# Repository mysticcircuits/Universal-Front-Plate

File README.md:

# Universal-Front-Plate

The Universal front plate was a project that I had high hopes for and while it did not accomplish what I originally set out to do with it I still found it quite useful.  Basically the board has 16 of the same footprint which can fit either an erthenvar style 3.5" jack, a board mount alpha pot or a sideways SPDT toggle switch.  There is also a set of 8 LEDs and their dedicated current limiting resistors going down the middle and hooked up to a trimmer which controls the overall brightness. All of these components are wired to some headers going along each side of the board so that a component board can be attached.  My idea was that this project would allow people to breadboard their own ideas while having a simple board which could handle various panel configurations and also maybe have some panels with drill positions marked to make prototyping without panel wiring much quicker.  The problem became that components were crammed too close together: when pots are placed in adjacent positions, whether vertically or horizonally, knob tightness became a serious issue.  I could not use the space saving "plastic shaft" pots because the pots are oriented sideways and so the direction marker would be rotated by 90 degrees.  Even placing the pots diagonally posed some issues with spacing.  However I did make two designs with the UFP and I have a few more coming up, as well as possibly other version of the UFP which are less universal but which are more efficient in their use of space.

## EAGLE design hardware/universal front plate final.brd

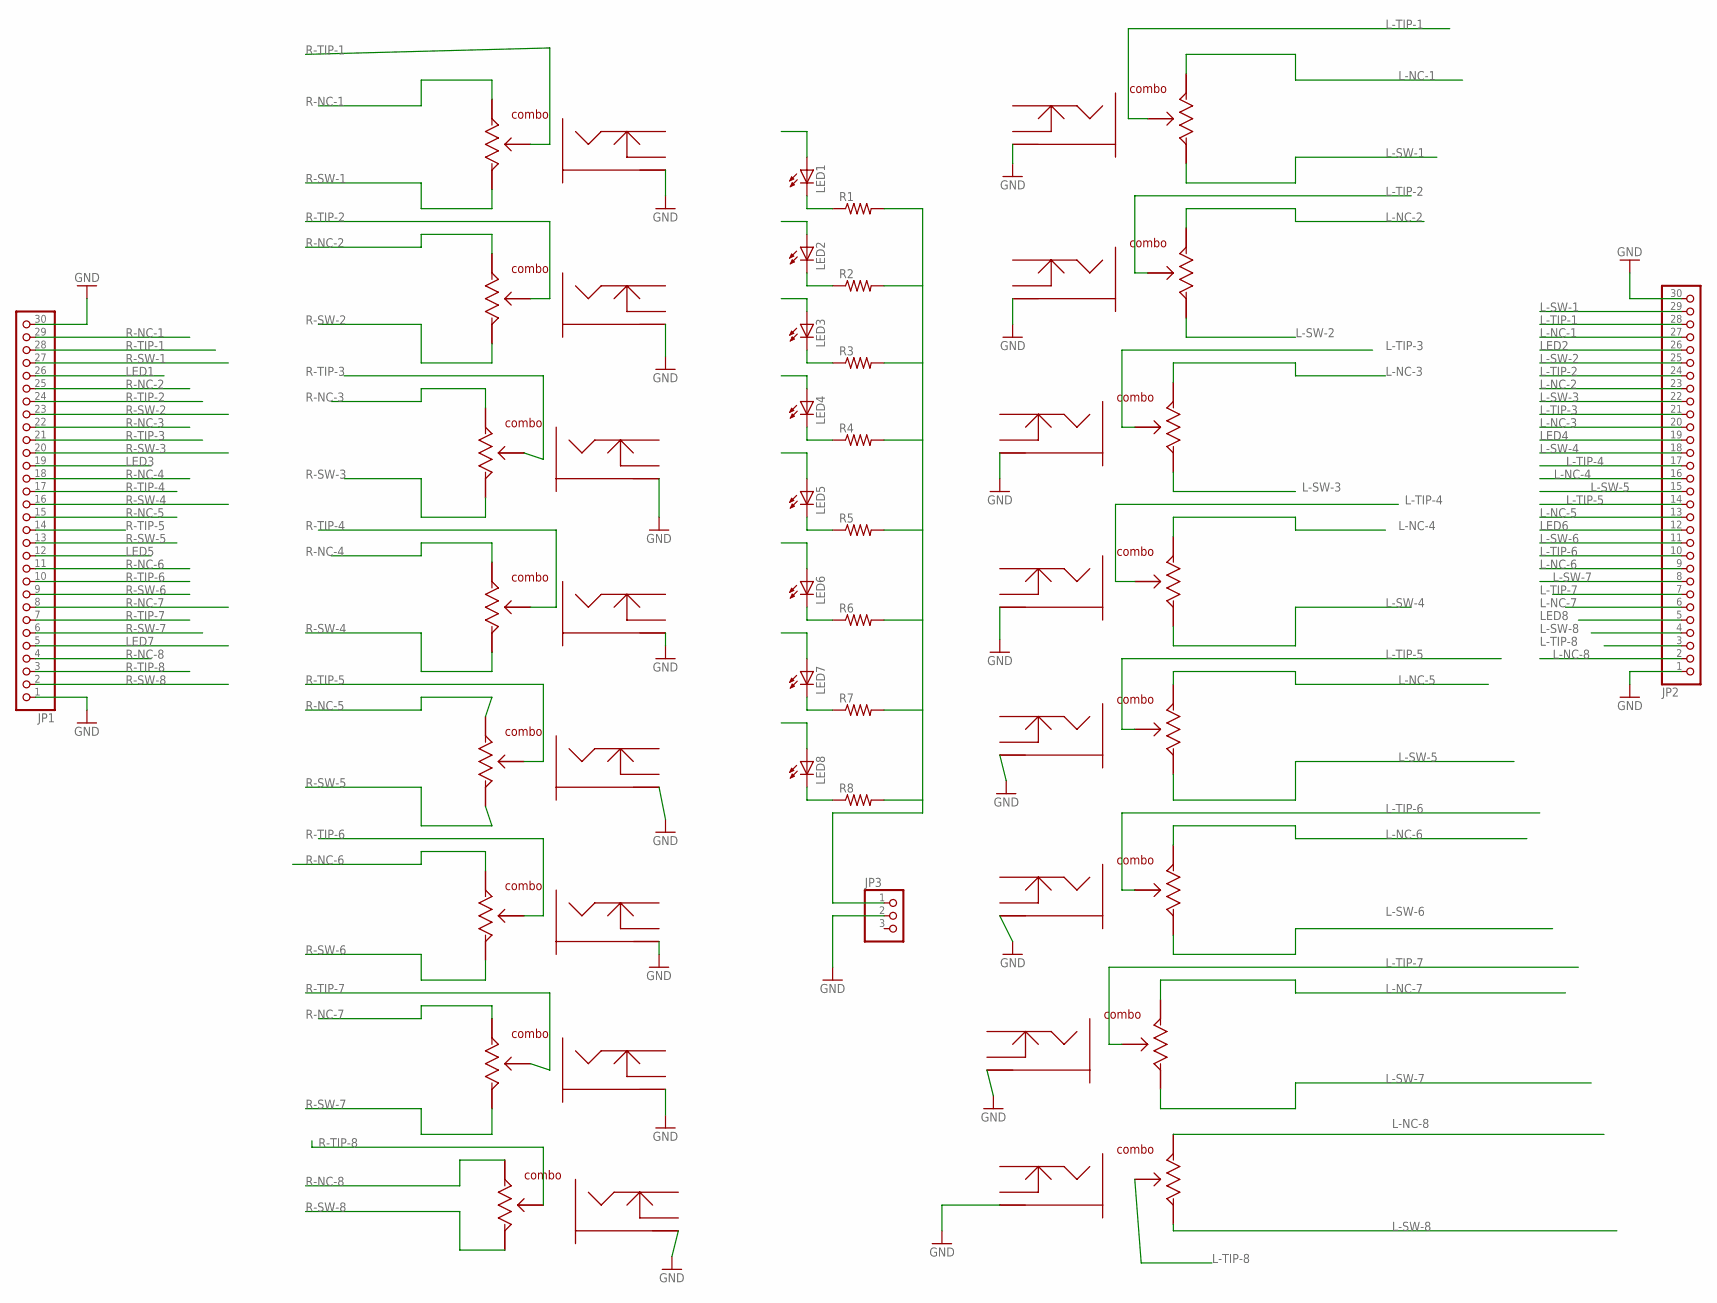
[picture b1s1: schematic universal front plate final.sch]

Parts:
JP1, JP2: PINHD-1X30; 1X30
JP3: PINHD-1X3; 1X03
LED1, LED2, LED3, LED4, LED5, LED6, LED7, LED8: LED3MM
R1, R2, R3, R4, R5, R6, R7, R8: R-US_0204/5; 0204/5
U$1, U$2, U$3, U$4, U$5, U$6, U$7, U$8, U$9, U$10, U$11, U$12, U$13, U$14, U$15, U$16: KOBICON-COMBO-NEW

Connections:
GND: JP1.1, JP1.30, JP2.1, JP2.30, JP3.2, U$1.GND (JACK-GND), U$1.GND2 (JACK-GND), U$2.GND (JACK-GND), U$2.GND2 (JACK-GND), U$3.GND (JACK-GND), U$3.GND2 (JACK-GND), U$4.GND (JACK-GND), U$4.GND2 (JACK-GND), U$5.GND (JACK-GND), U$5.GND2 (JACK-GND), U$6.GND (JACK-GND), U$6.GND2 (JACK-GND), U$7.GND (JACK-GND), U$7.GND2 (JACK-GND), U$8.GND (JACK-GND), U$8.GND2 (JACK-GND), U$9.GND (JACK-GND), U$9.GND2 (JACK-GND), U$10.GND (JACK-GND), U$10.GND2 (JACK-GND), U$11.GND (JACK-GND), U$11.GND2 (JACK-GND), U$12.GND (JACK-GND), U$12.GND2 (JACK-GND), U$13.GND (JACK-GND), U$13.GND2 (JACK-GND), U$14.GND (JACK-GND), U$14.GND2 (JACK-GND), U$15.GND (JACK-GND), U$15.GND2 (JACK-GND), U$16.GND (JACK-GND), U$16.GND2 (JACK-GND)
L-NC-1: JP2.27, U$8.JACK-MID (POT-L), U$8.POT-L
L-NC-2: JP2.23, U$9.JACK-MID (POT-L), U$9.POT-L
L-NC-3: JP2.20, U$10.JACK-MID (POT-L), U$10.POT-L
L-NC-4: JP2.16, U$11.JACK-MID (POT-L), U$11.POT-L
L-NC-5: JP2.13, U$12.JACK-MID (POT-L), U$12.POT-L
L-NC-6: JP2.9, U$13.JACK-MID (POT-L), U$13.POT-L
L-NC-7: JP2.6, U$14.JACK-MID (POT-L), U$14.POT-L
L-NC-8: JP2.2, U$15.JACK-MID (POT-L), U$15.POT-L
L-SW-1: JP2.29, U$8.JACK-BOT (POT-R), U$8.POT-R
L-SW-2: JP2.25, U$9.JACK-BOT (POT-R), U$9.POT-R
L-SW-3: JP2.22, U$10.JACK-BOT (POT-R), U$10.POT-R
L-SW-4: JP2.18, U$11.JACK-BOT (POT-R), U$11.POT-R
L-SW-5: JP2.15, U$12.JACK-BOT (POT-R), U$12.POT-R
L-SW-6: JP2.11, U$13.JACK-BOT (POT-R), U$13.POT-R
L-SW-7: JP2.8, U$14.JACK-BOT (POT-R), U$14.POT-R
L-SW-8: JP2.4, U$15.JACK-BOT (POT-R), U$15.POT-R
L-TIP-1: JP2.28, U$8.JACK-TOP (POT-MID), U$8.POT-MID
L-TIP-2: JP2.24, U$9.JACK-TOP (POT-MID), U$9.POT-MID
L-TIP-3: JP2.21, U$10.JACK-TOP (POT-MID), U$10.POT-MID
L-TIP-4: JP2.17, U$11.JACK-TOP (POT-MID), U$11.POT-MID
L-TIP-5: JP2.14, U$12.JACK-TOP (POT-MID), U$12.POT-MID
L-TIP-6: JP2.10, U$13.JACK-TOP (POT-MID), U$13.POT-MID
L-TIP-7: JP2.7, U$14.JACK-TOP (POT-MID), U$14.POT-MID
L-TIP-8: JP2.3, U$15.JACK-TOP (POT-MID), U$15.POT-MID
LED1: JP1.26, LED1.A
LED2: JP2.26, LED2.A
LED3: JP1.19, LED3.A
LED4: JP2.19, LED4.A
LED5: JP1.12, LED5.A
LED6: JP2.12, LED6.A
LED7: JP1.5, LED7.A
LED8: JP2.5, LED8.A
unnamed: LED8.K (C), R8.1
unnamed: JP3.1, R1.2, R2.2, R3.2, R4.2, R5.2, R6.2, R7.2, R8.2
unnamed: LED1.K (C), R1.1
unnamed: LED2.K (C), R2.1
unnamed: LED3.K (C), R3.1
unnamed: LED4.K (C), R4.1
unnamed: LED5.K (C), R5.1
unnamed: LED6.K (C), R6.1
unnamed: LED7.K (C), R7.1
R-NC-1: JP1.29, U$1.JACK-MID (POT-L), U$1.POT-L
R-NC-2: JP1.25, U$2.JACK-MID (POT-L), U$2.POT-L
R-NC-3: JP1.22, U$3.JACK-MID (POT-L), U$3.POT-L
R-NC-4: JP1.18, U$4.JACK-MID (POT-L), U$4.POT-L
R-NC-5: JP1.15, U$5.JACK-MID (POT-L), U$5.POT-L
R-NC-6: JP1.11, U$6.JACK-MID (POT-L), U$6.POT-L
R-NC-7: JP1.8, U$7.JACK-MID (POT-L), U$7.POT-L
R-NC-8: JP1.4, U$16.JACK-MID (POT-L), U$16.POT-L
R-SW-1: JP1.27, U$1.JACK-BOT (POT-R), U$1.POT-R
R-SW-2: JP1.23, U$2.JACK-BOT (POT-R), U$2.POT-R
R-SW-3: JP1.20, U$3.JACK-BOT (POT-R), U$3.POT-R
R-SW-4: JP1.16, U$4.JACK-BOT (POT-R), U$4.POT-R
R-SW-5: JP1.13, U$5.JACK-BOT (POT-R), U$5.POT-R
R-SW-6: JP1.9, U$6.JACK-BOT (POT-R), U$6.POT-R
R-SW-7: JP1.6, U$7.JACK-BOT (POT-R), U$7.POT-R
R-SW-8: JP1.2, U$16.JACK-BOT (POT-R), U$16.POT-R
R-TIP-1: JP1.28, U$1.JACK-TOP (POT-MID), U$1.POT-MID
R-TIP-2: JP1.24, U$2.JACK-TOP (POT-MID), U$2.POT-MID
R-TIP-3: JP1.21, U$3.JACK-TOP (POT-MID), U$3.POT-MID
R-TIP-4: JP1.17, U$4.JACK-TOP (POT-MID), U$4.POT-MID
R-TIP-5: JP1.14, U$5.JACK-TOP (POT-MID), U$5.POT-MID
R-TIP-6: JP1.10, U$6.JACK-TOP (POT-MID), U$6.POT-MID
R-TIP-7: JP1.7, U$7.JACK-TOP (POT-MID), U$7.POT-MID
R-TIP-8: JP1.3, U$16.JACK-TOP (POT-MID), U$16.POT-MID

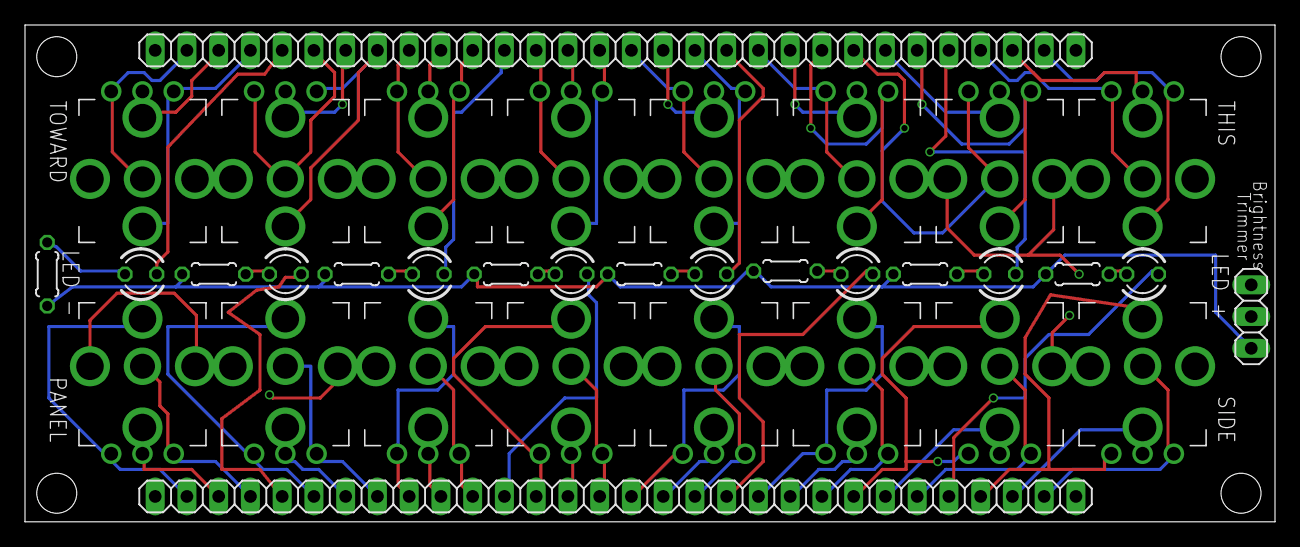
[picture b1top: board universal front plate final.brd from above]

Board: 2 copper layers, 100.0 x 39.7 mm, 35 parts (0 on the bottom side), 66 nets.

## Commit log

2016-05-10 Create blah
2016-05-10 Create licence
